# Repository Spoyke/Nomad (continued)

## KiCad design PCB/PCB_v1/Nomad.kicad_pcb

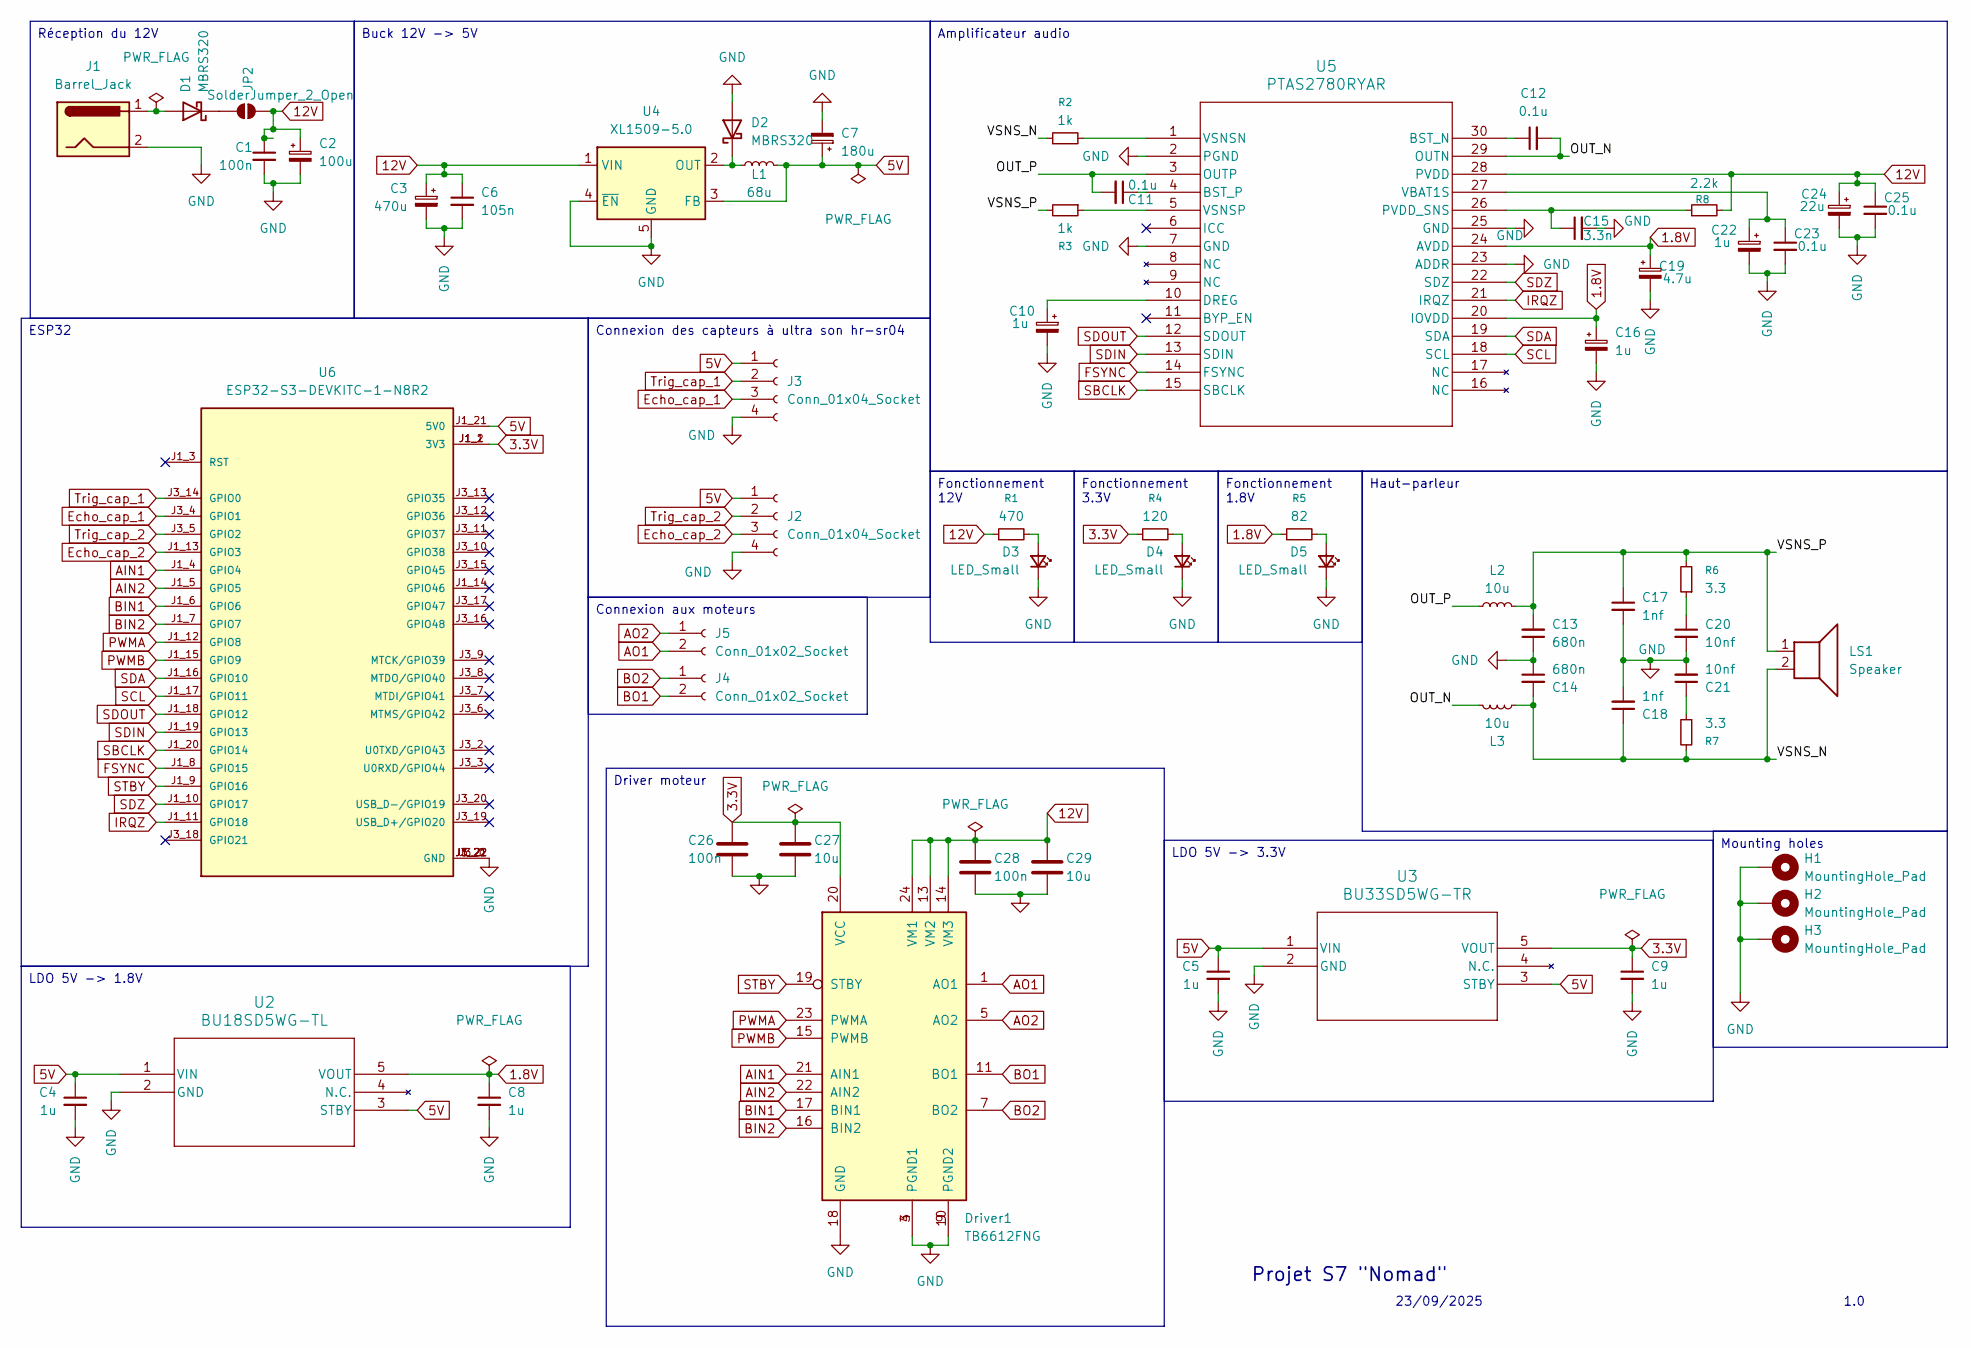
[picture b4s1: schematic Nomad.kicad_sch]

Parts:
C1: 100n; C_0603_1608Metric_Pad1.08x0.95mm_HandSolder
C2: 100u; C_0603_1608Metric_Pad1.08x0.95mm_HandSolder
C3: 470u; C_0603_1608Metric_Pad1.08x0.95mm_HandSolder
C4, C5, C8, C9, C10, C16, C22: 1u; C_0603_1608Metric_Pad1.08x0.95mm_HandSolder
C6: 105n; C_0603_1608Metric_Pad1.08x0.95mm_HandSolder
C7: 180u; C_0603_1608Metric_Pad1.08x0.95mm_HandSolder
C11, C12, C23, C25: 0.1u; C_0603_1608Metric_Pad1.08x0.95mm_HandSolder
C13, C14: 680n; C_0603_1608Metric_Pad1.08x0.95mm_HandSolder
C15: 3.3n; C_0603_1608Metric_Pad1.08x0.95mm_HandSolder
C17, C18: 1nf; C_0603_1608Metric_Pad1.08x0.95mm_HandSolder
C19: 4.7u; C_0603_1608Metric_Pad1.08x0.95mm_HandSolder
C20, C21: 10nf; C_0603_1608Metric_Pad1.08x0.95mm_HandSolder
C24: 22u; C_0603_1608Metric_Pad1.08x0.95mm_HandSolder
C26, C28: 100n; C_0402_1005Metric
C27, C29: 10u; C_0805_2012Metric
D1, D2: MBRS320; D_SMC
D3, D4, D5: LED_Small; LED_0603_1608Metric_Pad1.05x0.95mm_HandSolder
Driver1: TB6612FNG; SSOP-24_5.3x8.2mm_P0.65mm
H1, H2, H3: MountingHole_Pad; MountingHole_3.2mm_M3_DIN965_Pad
J1: Barrel_Jack; BarrelJack_CUI_PJ-102AH_Horizontal
J2, J3: Conn_01x04_Socket; PinSocket_1x04_P1.27mm_Vertical
J4, J5: Conn_01x02_Socket; PinHeader_1x02_P1.27mm_Vertical
JP2: SolderJumper_2_Open; SolderJumper-2_P1.3mm_Open_TrianglePad1.0x1.5mm
L1: 68u; L_0805_2012Metric_Pad1.05x1.20mm_HandSolder
L2, L3: 10u; L_0805_2012Metric_Pad1.05x1.20mm_HandSolder
LS1: Speaker; JST_EH_B2B-EH-A_1x02_P2.50mm_Vertical
R1: 470; R_0603_1608Metric_Pad0.98x0.95mm_HandSolder
R2, R3: 1k; R_0603_1608Metric_Pad0.98x0.95mm_HandSolder
R4: 120; R_0603_1608Metric_Pad0.98x0.95mm_HandSolder
R5: 82; R_0603_1608Metric_Pad0.98x0.95mm_HandSolder
R6, R7: 3.3; R_0603_1608Metric_Pad0.98x0.95mm_HandSolder
R8: 2.2k; R_0603_1608Metric_Pad0.98x0.95mm_HandSolder
U2: BU18SD5WG-TL; SSOP5_ROM-L
U3: BU33SD5WG-TR; SSOP5_ROM-L
U4: XL1509-5.0; SOIC-8_3.9x4.9mm_P1.27mm
U5: PTAS2780RYAR; VQFN-HR_RYA_TEX
U6: ESP32-S3-DEVKITC-1-N8R2; XCVR_ESP32-S3-DEVKITC-1-N8R2; PARTREV V1

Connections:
1.8V: C8.1, C16.1, C19.1, R5.1, U2.5 (VOUT), U5.20 (IOVDD), U5.24 (AVDD)
3.3V: C9.1, C26.1, C27.1, Driver1.20 (VCC), R4.1, U3.5 (VOUT), U6.J1_1 (3V3), U6.J1_2 (3V3)
5V: C4.1, C5.1, C7.1, J2.1, J3.1, L1.2, U2.1 (VIN), U2.3 (STBY), U3.1 (VIN), U3.3 (STBY), U4.3 (FB), U6.J1_21 (5V0)
12V: C1.1, C2.1, C3.1, C6.1, C24.1, C25.1, C28.1, C29.1, Driver1.13 (VM2), Driver1.14 (VM3), Driver1.24 (VM1), JP2.2 (B), R1.1, R8.2, U4.1 (VIN), U5.28 (PVDD)
/OUT_N: C12.2, L3.1, U5.29 (OUTN)
/OUT_P: C11.2, L2.1, U5.3 (OUTP)
/VSNS_N: C14.2, C18.1, L3.2, LS1.2, R2.1, R7.2
/VSNS_P: C13.2, C17.1, L2.2, LS1.1, R3.2, R6.2
AIN1: Driver1.21 (AIN1), U6.J1_4 (GPIO4)
AIN2: Driver1.22 (AIN2), U6.J1_5 (GPIO5)
AO1: Driver1.1 (AO1), Driver1.2 (AO1), J5.2
AO2: Driver1.5 (AO2), Driver1.6 (AO2), J5.1
BIN1: Driver1.17 (BIN1), U6.J1_6 (GPIO6)
BIN2: Driver1.16 (BIN2), U6.J1_7 (GPIO7)
BO1: Driver1.11 (BO1), Driver1.12 (BO1), J4.2
BO2: Driver1.7 (BO2), Driver1.8 (BO2), J4.1
Echo_cap_1: J3.3, U6.J3_4 (GPIO1)
Echo_cap_2: J2.3, U6.J1_13 (GPIO3)
FSYNC: U5.14 (FSYNC), U6.J1_8 (GPIO15)
GND: C1.2, C2.2, C3.2, C4.2, C5.2, C6.2, C7.2, C8.2, C9.2, C10.2, C13.1, C14.1, C15.2, C16.2, C17.2, C18.2, C19.2, C20.2, C21.2, C22.2, C23.2, C24.2, C25.2, C26.2, C27.2, C28.2, C29.2, D2.2 (A), D3.1 (K), D4.1 (K), D5.1 (K), Driver1.3 (PGND1), Driver1.4 (PGND1), Driver1.9 (PGND2), Driver1.10 (PGND2), Driver1.18 (GND), H1.1, H2.1, H3.1, J1.2, J2.4, J3.4, U2.2 (GND), U3.2 (GND), U4.4 (~EN), U4.5 (GND), U4.6 (GND), U4.7 (GND), U4.8 (GND), U5.2 (PGND), U5.7 (GND), U5.23 (ADDR), U5.25 (GND), U6.J1_22 (GND), U6.J3_1 (GND), U6.J3_21 (GND), U6.J3_22 (GND)
IRQZ: U5.21 (IRQZ), U6.J1_11 (GPIO18)
unnamed: C20.1, R6.1
unnamed: C21.1, R7.1
unnamed: D1.2 (A), J1.1
unnamed: D1.1 (K), JP2.1 (A)
unnamed: D2.1 (K), L1.1, U4.2 (OUT)
unnamed: D3.2 (A), R1.2
unnamed: D4.2 (A), R4.2
unnamed: D5.2 (A), R5.2
unnamed: C12.1, U5.30 (BST_N)
unnamed: C11.1, U5.4 (BST_P)
unnamed: C10.1, U5.10 (DREG)
unnamed: C15.1, R8.1, U5.26 (PVDD_SNS)
unnamed: C22.1, C23.1, U5.27 (VBAT1S)
unnamed: R2.2, U5.1 (VSNSN)
unnamed: R3.1, U5.5 (VSNSP)
PWMA: Driver1.23 (PWMA), U6.J1_12 (GPIO8)
PWMB: Driver1.15 (PWMB), U6.J1_15 (GPIO9)
SBCLK: U5.15 (SBCLK), U6.J1_20 (GPIO14)
SCL: U5.18 (SCL), U6.J1_17 (GPIO11)
SDA: U5.19 (SDA), U6.J1_16 (GPIO10)
SDIN: U5.13 (SDIN), U6.J1_19 (GPIO13)
SDOUT: U5.12 (SDOUT), U6.J1_18 (GPIO12)
SDZ: U5.22 (SDZ), U6.J1_10 (GPIO17)
STBY: Driver1.19 (STBY), U6.J1_9 (GPIO16)
Trig_cap_1: J3.2, U6.J3_14 (GPIO0)
Trig_cap_2: J2.2, U6.J3_5 (GPIO2)

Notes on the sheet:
23/09/2025
Projet S7 "Nomad"
1.0
Réception du 12V
Mounting holes
LDO 5V -> 3.3V
Fonctionnement 3.3V
Haut-parleur
Connexion aux moteurs
Driver moteur
ESP32
Connexion des capteurs à ultra son hr-sr04
Fonctionnement 1.8V
LDO 5V -> 1.8V
Amplificateur audio
Buck 12V -> 5V
Fonctionnement 12V

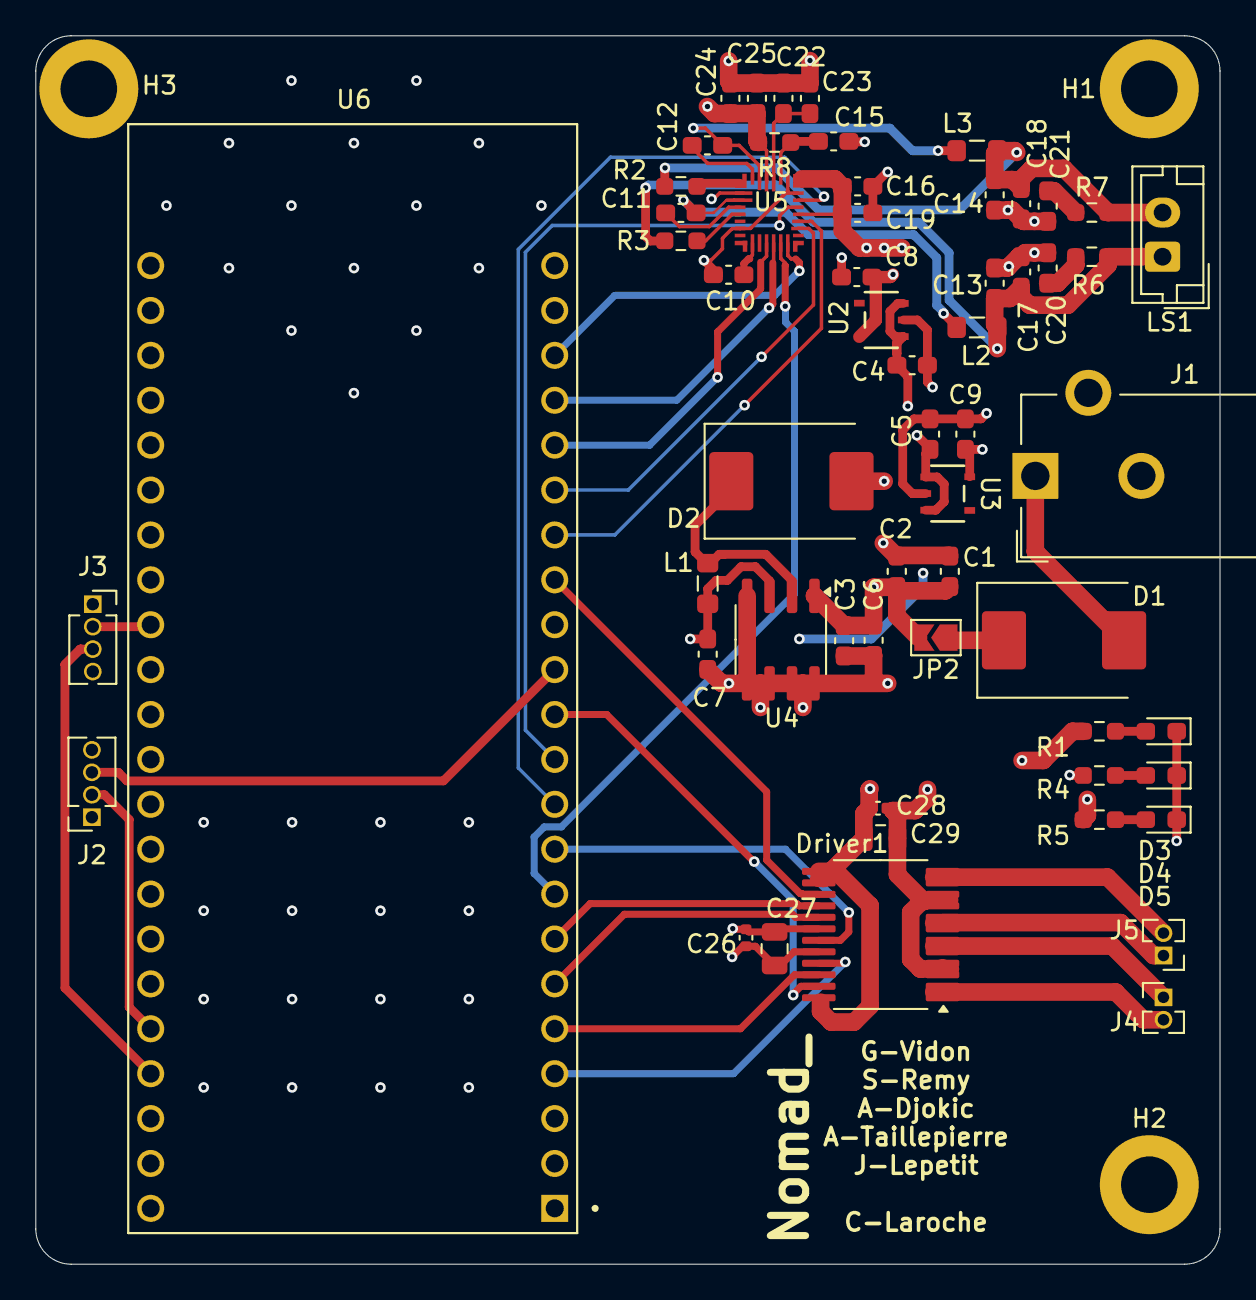
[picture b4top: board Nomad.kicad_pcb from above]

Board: 4 copper layers, 67.0 x 69.5 mm, 61 parts (0 on the bottom side), 47 nets.

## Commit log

2025-09-23 Nouvelle version schéma kicad
    changement de nom + nouveau schéma elec
2025-09-23 retouches schema elec
2025-09-23 Début routage
    déput placement des composants sur pcb, et capa de decouplage relativement aux composants
2025-09-25 Merged branches
2025-09-26 small fixes
    resolved erc errors
2025-09-30 routage pcb
    finitions placement composants + routage
2025-09-30 Add files via upload
    Partie informatique lié a capter un signal wifi/bluetooth
2025-09-30 Fin routage
    Fin routage sauf pour esp
2025-09-30 Ajout de la partie informatique
2025-09-30 Ajout de l'application faite par axel
2025-10-06 Finished routing and silkscreen placement
    todo Gerber
2025-10-06 update partie info
2025-10-07 schéma ancien routage final ver
2025-10-07 encore plus de routage :(
    Todo, rapprocher au max capa de découplage
    grossir pistes alim au max
2025-10-08 Fin routage
    pls j'espère que c'est fini
2025-10-08 fin routage
    ok normalement là c'est bon
2025-10-14 Réorganisation des dossiers
    Séparation de la partie info et la partie élec
2025-10-15 Elargissement des pistes d'alim en interne
2025-10-15 Changements demandés par prof
2025-10-15 see prev commit message
2025-10-21 PCB Finalise
    finalisation pcb, création fichiers gerber
2025-10-26 update partie info axel
2025-10-26 code esp32
2025-10-26 Update README with Séance 5 notes
    Added notes about LM386 usage and audio amplifier tests.
2025-11-04 Revise team progress updates in README
    Updated project progress notes for team members.
2025-11-04 Update team progress and next steps in README
    Added updates on tasks and next steps for the team.
2025-11-05 Mettre à jour les progrès de l'équipe dans le README
    Ajout des mises à jour des membres de l'équipe concernant la synchronisation des ESP32, le multithreading et d'autres tâches en cours.
2025-11-19 recherche composants
2025-11-19 Update README with session 7 details
    Added details for session 7 including tasks and responsibilities.
2025-11-22 Update README with ESP32 project details
    Added details about distance measurement and sound synchronization with ESP32 devices.
2025-11-25 Update README with session 7 details
    Added details about session 7 and sound synchronization.
2025-11-25 Update README with project progress details
    Added updates on ultrasonic sensor functionality and motor work.
2025-11-26 Revise session number and add new contributions
    Updated session details and added new contributions from Gabriel.
2025-12-02 Reroganisation fichier + création docs pour v2 des pcb
    voir titre
2025-12-02 Update project status and tasks in README
2025-12-02 Document Simon's PCB testing findings
    Added details about Simon's testing of the PCB and issues encountered.
2025-12-03 Update README with team testing feedback
    Added comments from team members regarding testing and issues encountered with components.
2025-12-06 update info
2025-12-09 Remove Nomad PCB and schematic files
    Deleted all KiCad project, schematic, PCB, and backup files for both 'Carte puissance' and 'Carte signal' boards in PCB_v2, as well as a lock file in PCB_v1. This cleans up obsolete or unused design 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
2025-12-09 creation fichiers
2025-12-09 Création du pcb cmd
2025-12-10 Update README with Gabriel's project contributions
    Added notes on Gabriel's work with components and PCB projects.
2025-12-13 Update README with Simon's PCB and robot positioning details
    Added updates on Simon's work regarding the audio PCB design and robot positioning.
2025-12-13 Ajout du diapo
2025-12-14 Change communication protocols to WebSocket for Raspberry Pi
    Updated communication protocols for mobile app and Raspberry Pi.
2025-12-16 pcb commande empruntes + debut routage
2025-12-17 see previous commit
2025-12-29 Change music streaming server from WebSocket to Icecast
    Updated the music streaming server description from WebSocket to Icecast.
2026-01-02 Update Séance 11 notes in README
    Added updates on PCB audio part and current consumption analysis.
2026-01-03 Update README with project progress and remove section
    Removed Julie's section and added updates from Gabriel and Simon.
2026-01-13 added mpu6050 link to sources
2026-01-13 PCB méca
    Fusionner la partie méca avec alim
2026-01-13 Add new KiCad PCB and schematic files for Partie_cmd
    Added new footprints, backup files, and autosave files for the Partie_cmd project in PCBs_v2, including ESP32 and SSOP5 footprints. Updated Partie_cmd.kicad_pcb, Partie_cmd.kicad_sch, and fp-lib-tabl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
2026-01-13 Ajout PCB audio
2026-01-13 Add planning section for 2nd semester
    Added a section for the planning of the second semester with a link to the calendar.
2026-01-13 fin schéma + Routage PCB cmd
2026-01-13 Update README with Simon's progress
    Added updates on Simon's tasks regarding planning and audio routing.
2026-01-13 Update README with Gabriel's progress on CMD card
    Added updates from Gabriel regarding the CMD card and audio routing.
2026-01-20 Update README with Julie's tasks and responsibilities
    Ajout des tâches de Julie concernant les capteurs et le routage.
2026-01-20 MAJ PCB audio
2026-01-20 Update README with Séance 13 details
    Added notes for Séance 13 regarding PCB routing.
2026-01-20 Routage pcb cmd
2026-01-20 cr de seance gab 20/01
2026-01-21 Document voice transmission complication
    Added a note about voice transmission issues related to data format.
2026-01-24 Modification du schéma et du routage de la partie audio
2026-01-27 Fin routage pcb cmd
    :(
2026-01-27 fin routage pcb 1.1
2026-01-27 Fin routage 1.2
    pour de vrai cette foix?
2026-01-27 replacement trous de perçage
2026-01-27 Update README with Séance 14 details
    Added notes for Séance 14 regarding PCB routing.
2026-01-27 fin du routage
    svpsvpsvpsvpsvp
2026-01-27 Modification du PCB audio pour avoir un connecteur de 14 broches
2026-01-30 correction erreurs
2026-01-30 Update README with audio PCB routing information
    Added details about audio PCB routing and testing.
2026-02-03 formating
2026-02-03 Correct resource links formatting
    Fixed formatting of resource links in README.
2026-02-03 Update README with sensor and prototype details
2026-02-03 Add Julie's study of sensors to README
2026-02-04 Document amplifier configuration challenges in README
    Added notes on amplifier issues with the old PCB and configuration attempts.
2026-02-07 Nettoyage des fichiers de la partie PCB
2026-02-07 qques legeres modifs
2026-02-08 Ajout de la parie info d'axel
2026-02-10 Création code controle moteurs
2026-02-10 Update README with session 16 notes
    Added details about session 16 and communication issues with TAS2780.
2026-02-10 Ajout du code de test du TAS2780 et modification du readme
2026-02-11 Modification du programme du TAS2780
2026-02-14 Modification du PCB de la partie audio pour avoir une perle de ferrite avec une ampreinte plus grande
2026-02-16 Suppression d'une ancienne version du projet qui était toujours dans la version actuelle
2026-02-17 Compte rendu séances 15 et 16 GV
2026-02-17 comment changes
2026-02-17 Change session titles to headings in README
    Updated session headings in README to improve clarity and organization.
2026-02-17 Update README with session 17 details
    Added notes for session 17 regarding soldering the board.
2026-02-23 Commande_Julie
2026-03-03 pcbss
2026-03-03 Update README with latest project progress
    Added updates regarding PCB Commande and other progress.
2026-03-03 Parti info
2026-03-04 schema et pcb update
2026-03-10 changements partie info
    création code tests encodeurs
2026-03-10 Update README with session 18 details
    Added details for session 18 regarding PCB audio testing.
2026-03-13 New pcb avec des erreurs
2026-03-13 PCB final
2026-03-13 edit pcb
2026-03-14 edit 3v3 zone
2026-03-17 Detection sens de rotation et valeur de rotation
2026-03-17 Last pcbss
2026-03-17 Finitions pcb
2026-03-17 session update
2026-03-18 Finitions pcb cmd
2026-03-18 hein
2026-03-24 Update README with recent progress on PCB and encoders
    Added updates for Julie's work on PCB and encoder testing.
2026-03-24 Update README with Séance 20 details
    Added details for Séance 20 and updated resources section.
2026-03-24 Changement affichage retour encodeurs
2026-03-24 Séance 20 GV
2026-04-07 adaptation code pour carte
    fonctionnement encodeurs. Rotation moteurs non fonctionelle. Tests leds verification
2026-04-07 Update README with Séance extra 21 notes
    Added notes from Séance extra 21 regarding PCB testing and audio issues.
2026-04-15 Ajout du support de la présentation
2026-04-19 modif parti info
